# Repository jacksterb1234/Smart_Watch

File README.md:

# Smart Watch — Custom KiCad Smartwatch PCB

A fully custom smartwatch designed from the ground up, featuring a purpose-built PCB, BLE connectivity, and a 3D-printed case. Designed for complete control over hardware and software integration.

> Integration testing projected to begin July 2026.

## Features

- **MCU:** Nordic nRF54L15 — ultra-low power with integrated Bluetooth LE
- **Step counting** via IMU
- **Heart rate sensing**
- **Touchscreen display**
- **Music control** and **notification vibration** (haptic)
- **USB-C charging**
- **Custom 3D-printed case** — ~30% lighter than off-the-shelf alternatives, fully personalizable
- Designed for **JLCPCB assembly**

## Repository Structure

```
Smart_Watch/
├── Architecture.kicad_sch   # Top-level architecture schematic
├── MCU.kicad_sch            # nRF54L15 MCU schematic
├── Power.kicad_sch          # Power management schematic
├── Peripherals.kicad_sch   # Sensors & peripheral schematic
├── Smart_Watch.kicad_pcb   # PCB layout
├── Smart_Watch.pdf          # Full schematic export
├── Smart_Watch.pretty/     # Custom KiCad footprints
├── Smart_Watch.3dshapes/   # 3D models for PCB components
├── ZIF.pretty/              # ZIF connector footprints
├── B2B_PH_SM4_TB/          # Board-to-board connector footprints
├── Backpack_Board/         # Backpack extension board
├── Case/                   # 3D-printable case files
└── jlcpcb/                  # JLCPCB production files (Gerbers, BOM, CPL)
```

## Tools Used

- **KiCad** — Schematic capture and PCB layout
- **JLCPCB** — PCB fabrication and SMT assembly
- **SolidWorks / Fusion360** — Case design

## Key Components

| Component | Function |
|-----------|----------|
| nRF54L15 | MCU with integrated BLE |
| Heart rate sensor | Optical heart rate monitoring |
| IMU | Step counting and motion sensing |
| Touchscreen | User interface display |
| USB-C charger IC | Battery charging via USB-C |

## Author

**Jackson Barber** — [github.com/jacksterb1234](https://github.com/jacksterb1234)

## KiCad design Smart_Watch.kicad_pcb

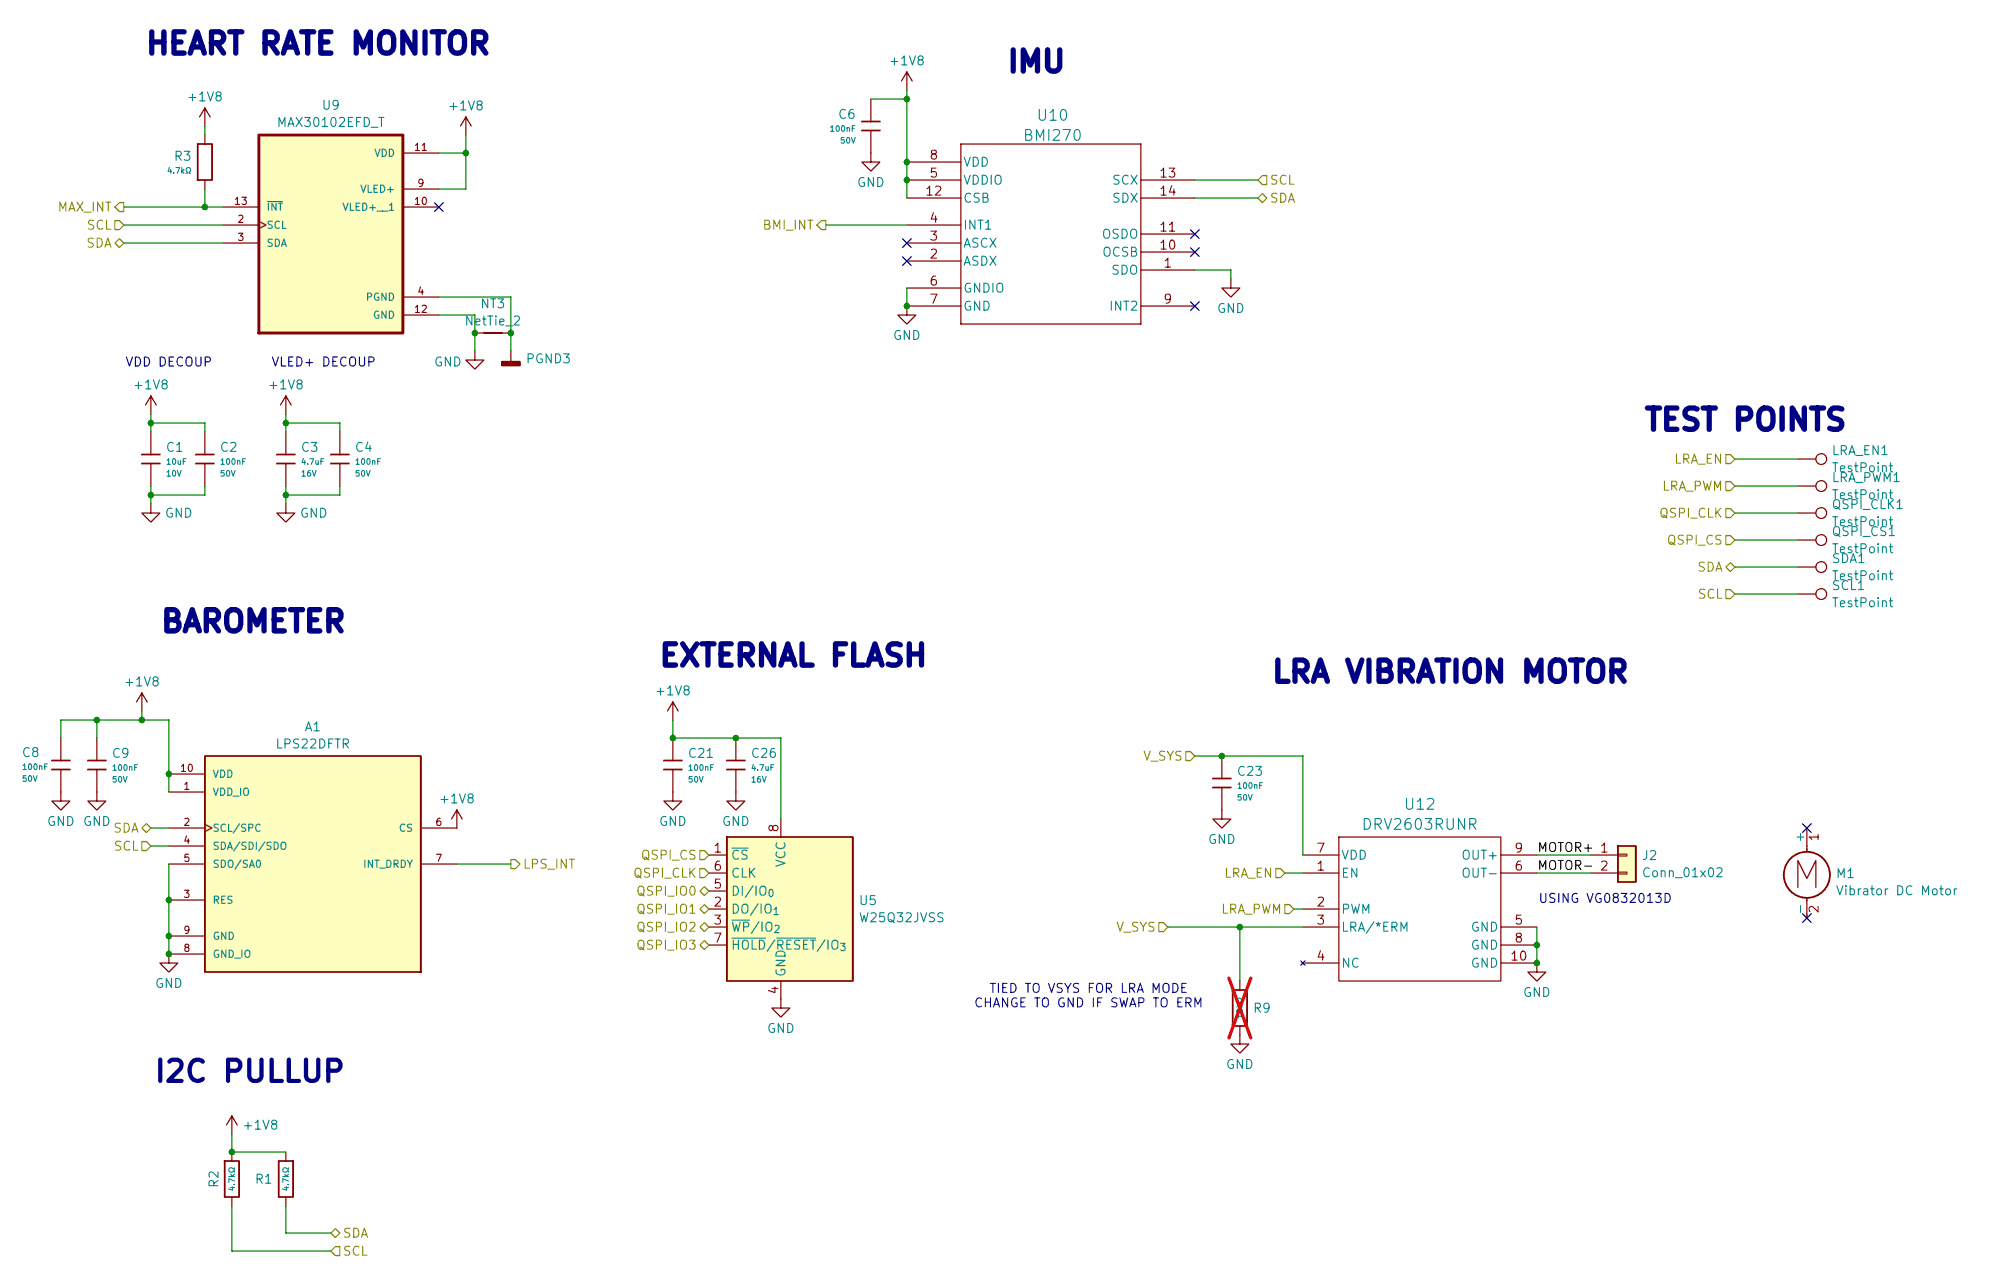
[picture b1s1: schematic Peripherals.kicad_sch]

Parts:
A1: LPS22DFTR; XDCR_LPS22DFTR; PARTREV 3
C1: 10uF; C_0603; Voltage Rated 10V; Tolerance ±10%; Part CL10A106KP8NNNC; LCSC C19702
C2, C4, C6, C8, C9, C21, C23: 100nF; C_0603; Voltage Rated 50V; Tolerance ±10%; Part CC0603KRX7R9BB104; LCSC C14663
C3, C26: 4.7uF; C_0603; Voltage Rated 16V; Tolerance ±10%; Part CL10A475KO8NNNC; LCSC C19666
J2: Conn_01x02; 1x02_1x1mm
LRA_EN1: TestPoint; TestPoint_Pad_1.0x1.0mm
LRA_PWM1: TestPoint; TestPoint_Pad_1.0x1.0mm
M1: Vibrator DC Motor; digikey# 1670-VC1027B902F-ND
NT3: NetTie_2; NetTie-2_SMD_Pad0.5mm
QSPI_CLK1: TestPoint; TestPoint_Pad_1.0x1.0mm
QSPI_CS1: TestPoint; TestPoint_Pad_1.0x1.0mm
R1, R2, R3: 4.7kΩ; R_0603; Overload Voltage (Max) 75V; Tolerance ±1%; Part 0603WAF4701T5E; LCSC C23162
R9: 10kΩ; R_0402; Overload Voltage (Max) 50V; Tolerance ±1%; Part 0402WGF1002TCE; LCSC C25744; not fitted
SCL1: TestPoint; TestPoint_Pad_1.0x1.0mm
SDA1: TestPoint; TestPoint_Pad_1.0x1.0mm
U5: W25Q32JVSS; SOIC-8_5.3x5.3mm_P1.27mm
U9: MAX30102EFD_T; XDCR_MAX30101EFD_
U10: BMI270; BMI270_BOS-L
U12: DRV2603RUNR; RUN10_TEX

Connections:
+1V8: A1.1 (VDD_IO), A1.6 (CS), A1.10 (VDD), C1.2, C2.2, C3.1, C4.1, C6.1, C8.1, C9.1, C21.1, C26.1, R1.1, R2.1, R3.2, U5.8 (VCC), U9.9 (VLED+), U9.11 (VDD), U10.5 (VDDIO), U10.8 (VDD), U10.12 (CSB); also elsewhere on the board
/Architecture/MCU/BMI_INT: U10.4 (INT1); also elsewhere on the board
/Architecture/MCU/LPS_INT: A1.7 (INT_DRDY); also elsewhere on the board
/Architecture/MCU/LRA_EN: LRA_EN1.1 (1_1), U12.1 (EN); also elsewhere on the board
/Architecture/MCU/LRA_PWM: LRA_PWM1.1 (1_1), U12.2 (PWM); also elsewhere on the board
/Architecture/MCU/MAX_INT: R3.1, U9.13 (~INT); also elsewhere on the board
/Architecture/MCU/QSPI_CLK: QSPI_CLK1.1 (1_1), U5.6 (CLK); also elsewhere on the board
/Architecture/MCU/QSPI_CS: QSPI_CS1.1 (1_1), U5.1 (~CS); also elsewhere on the board
/Architecture/MCU/QSPI_IO0: U5.5 (DI/IO_{0}); also elsewhere on the board
/Architecture/MCU/QSPI_IO1: U5.2 (DO/IO_{1}); also elsewhere on the board
/Architecture/MCU/QSPI_IO2: U5.3 (~WP/IO_{2}); also elsewhere on the board
/Architecture/MCU/QSPI_IO3: U5.7 (~HOLD/~RESET/IO_{3}); also elsewhere on the board
/Architecture/MCU/SCL: A1.4 (SDA/SDI/SDO), R2.2, SCL1.1 (1_1), U9.2 (SCL), U10.13 (SCX); also elsewhere on the board
/Architecture/MCU/SDA: A1.2 (SCL/SPC), R1.2, SDA1.1 (1_1), U9.3 (SDA), U10.14 (SDX); also elsewhere on the board
/Architecture/Peripherals/MOTOR+: J2.1, U12.9 (OUT+)
/Architecture/Peripherals/MOTOR-: J2.2, U12.6 (OUT-)
GND: A1.3 (RES), A1.5 (SDO/SA0), A1.8 (GND_IO), A1.9 (GND), C1.1, C2.1, C3.2, C4.2, C6.2, C8.2, C9.2, C21.2, C23.2, C26.2, NT3.1, R9.2, U5.4 (GND), U9.12 (GND), U10.1 (SDO), U10.6 (GNDIO), U10.7 (GND), U12.5 (GND), U12.8 (GND), U12.10 (GND); also elsewhere on the board
PGND3: NT3.2, U9.4 (PGND)
VSYS: C23.1, R9.1, U12.3 (LRA/*ERM), U12.7 (VDD); also elsewhere on the board

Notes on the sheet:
HEART RATE MONITOR
I2C PULLUP
USING VG0832013D
EXTERNAL FLASH
TIED TO VSYS FOR LRA MODE CHANGE TO GND IF SWAP TO ERM
VDD DECOUP
VLED+ DECOUP
BAROMETER
IMU
TEST POINTS
LRA VIBRATION MOTOR

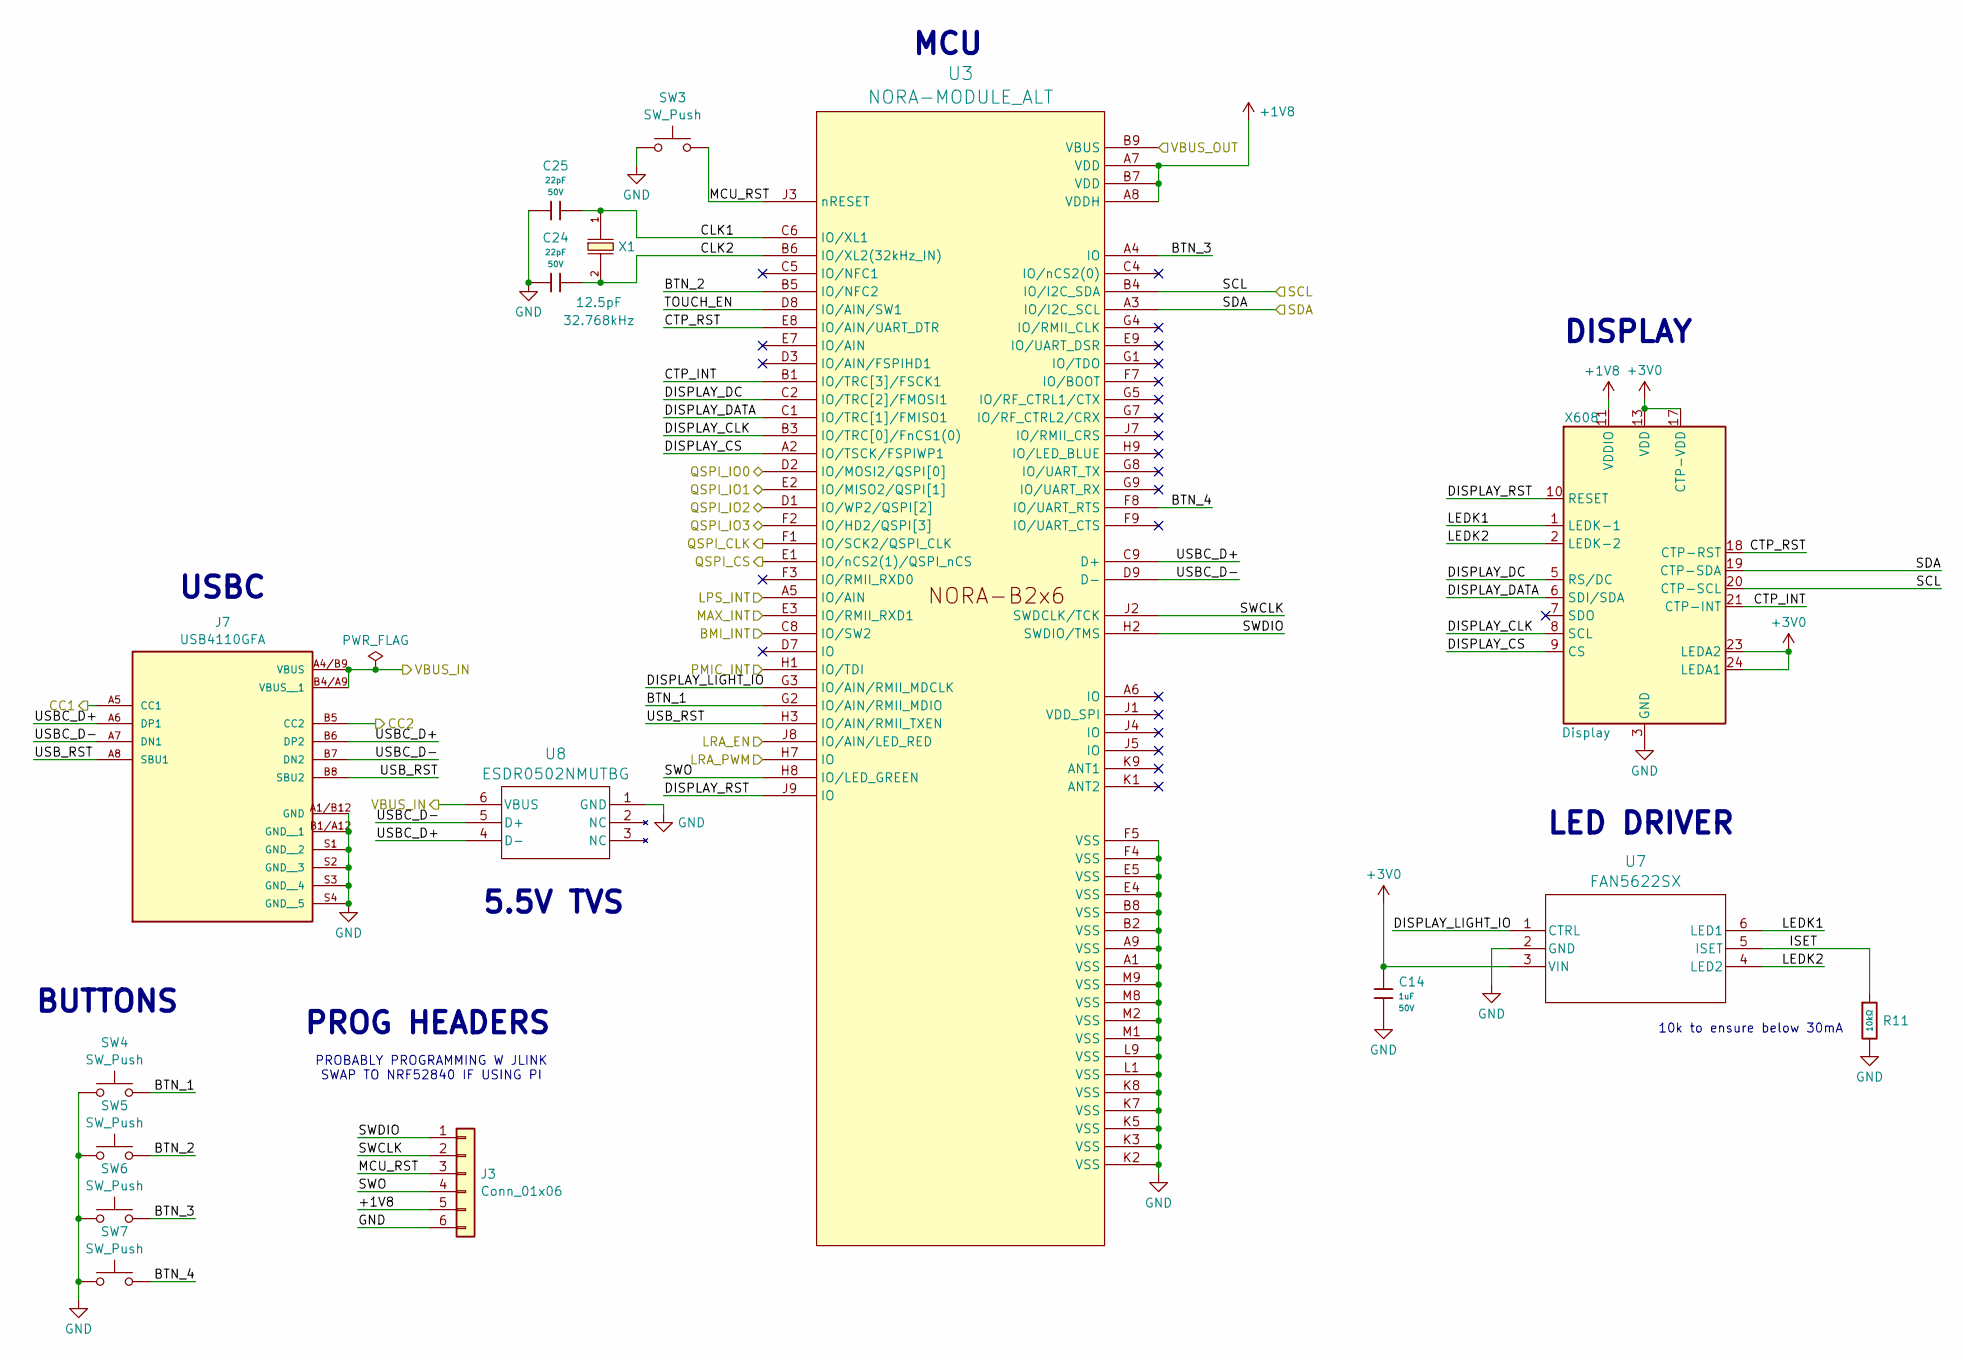
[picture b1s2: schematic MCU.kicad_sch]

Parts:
C14: 1uF; C_0603; Voltage Rated 50V; Tolerance ±10%; Part CL10A105KB8NNNC; LCSC C15849
C24, C25: 22pF; C_0603; Voltage Rated 50V; Tolerance ±5%; Part CL10C220JB8NNNC; LCSC C1653
J3: Conn_01x06; 2x03_1x1mm
J7: USB4110GFA; GCT_USB4110GFA
R11: 10kΩ; R_0603; Overload Voltage (Max) 75V; Tolerance ±1%; Part 0603WAF1002T5E; LCSC C25804
SW3: SW_Push; R_0805_2012Metric
SW4, SW5, SW6, SW7: SW_Push; SW_Push_1P1T-MP_NO_Horizontal_Alps_SKRTLAE010_3D
U3: NORA-MODULE_ALT; NORA_LGA82R_1430X1040X190_ANT; Manufacturer P/N NORA
U7: FAN5622SX; SSOT6_3X1P7_ONS-L
U8: ESDR0502NMUTBG; UDFN6_517AA_ONS-L
X1: Q13FC1350000400; FC-135R_L3.2-W1.5; Frequency Tolerance ±20ppm; Part Q13FC13500004; LCSC C32346
X608: Display; 24-PIN-ZIF

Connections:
+1V8: J3.5, U3.A7 (VDD), U3.A8 (VDDH), U3.B7 (VDD), X608.11 (VDDIO), X608.12 (VDDIO); also elsewhere on the board
+3V0: C14.1, U7.3 (VIN), X608.13 (VDD), X608.14 (VDD), X608.17 (CTP-VDD), X608.23 (LEDA2), X608.24 (LEDA1); also elsewhere on the board
/Architecture/MCU/BMI_INT: U3.C8 (IO/SW2); also elsewhere on the board
/Architecture/MCU/BTN_1: SW4.2, U3.G2 (IO/AIN/RMII_MDIO)
/Architecture/MCU/BTN_2: SW5.2, U3.B5 (IO/NFC2)
/Architecture/MCU/BTN_3: SW6.2, U3.A4 (IO)
/Architecture/MCU/BTN_4: SW7.2, U3.F8 (IO/UART_RTS)
/Architecture/MCU/CC1: J7.A5 (CC1); also elsewhere on the board
/Architecture/MCU/CC2: J7.B5 (CC2); also elsewhere on the board
/Architecture/MCU/CLK1: C25.2, U3.C6 (IO/XL1), X1.1
/Architecture/MCU/CLK2: C24.2, U3.B6 (IO/XL2(32kHz_IN)), X1.2
/Architecture/MCU/CTP_INT: U3.B1 (IO/TRC[3]/FSCK1), X608.21 (CTP-INT)
/Architecture/MCU/CTP_RST: U3.E8 (IO/AIN/UART_DTR), X608.18 (CTP-RST)
/Architecture/MCU/DISPLAY_CLK: U3.B3 (IO/TRC[0]/FnCS1(0)), X608.8 (SCL)
/Architecture/MCU/DISPLAY_CS: U3.A2 (IO/TSCK/FSPIWP1), X608.9 (CS)
/Architecture/MCU/DISPLAY_DATA: U3.C1 (IO/TRC[1]/FMISO1), X608.6 (SDI/SDA)
/Architecture/MCU/DISPLAY_DC: U3.C2 (IO/TRC[2]/FMOSI1), X608.5 (RS/DC)
/Architecture/MCU/DISPLAY_LIGHT_IO: U3.G3 (IO/AIN/RMII_MDCLK), U7.1 (CTRL)
/Architecture/MCU/DISPLAY_RST: U3.J9 (IO), X608.10 (RESET)
/Architecture/MCU/ISET: R11.1, U7.5 (ISET)
/Architecture/MCU/LEDK1: U7.6 (LED1), X608.1 (LEDK-1)
/Architecture/MCU/LEDK2: U7.4 (LED2), X608.2 (LEDK-2)
/Architecture/MCU/LPS_INT: U3.A5 (IO/AIN); also elsewhere on the board
/Architecture/MCU/LRA_EN: U3.J8 (IO/AIN/LED_RED); also elsewhere on the board
/Architecture/MCU/LRA_PWM: U3.H7 (IO); also elsewhere on the board
/Architecture/MCU/MAX_INT: U3.E3 (IO/RMII_RXD1); also elsewhere on the board
/Architecture/MCU/MCU_RST: J3.3, SW3.2, U3.J3 (nRESET)
/Architecture/MCU/PMIC_INT: U3.H1 (IO/TDI); also elsewhere on the board
/Architecture/MCU/QSPI_CLK: U3.F1 (IO/SCK2/QSPI_CLK); also elsewhere on the board
/Architecture/MCU/QSPI_CS: U3.E1 (IO/nCS2(1)/QSPI_nCS); also elsewhere on the board
/Architecture/MCU/QSPI_IO0: U3.D2 (IO/MOSI2/QSPI[0]); also elsewhere on the board
/Architecture/MCU/QSPI_IO1: U3.E2 (IO/MISO2/QSPI[1]); also elsewhere on the board
/Architecture/MCU/QSPI_IO2: U3.D1 (IO/WP2/QSPI[2]); also elsewhere on the board
/Architecture/MCU/QSPI_IO3: U3.F2 (IO/HD2/QSPI[3]); also elsewhere on the board
/Architecture/MCU/SCL: U3.B4 (IO/I2C_SDA), X608.20 (CTP-SCL); also elsewhere on the board
/Architecture/MCU/SDA: U3.A3 (IO/I2C_SCL), X608.19 (CTP-SDA); also elsewhere on the board
/Architecture/MCU/SWCLK: J3.2, U3.J2 (SWDCLK/TCK)
/Architecture/MCU/SWDIO: J3.1, U3.H2 (SWDIO/TMS)
/Architecture/MCU/SWO: J3.4, U3.H8 (IO/LED_GREEN)
/Architecture/MCU/TOUCH_EN: U3.D8 (IO/AIN/SW1)
/Architecture/MCU/USBC_D+: J7.A6 (DP1), J7.B6 (DP2), U3.C9 (D+), U8.4 (D-)
/Architecture/MCU/USBC_D-: J7.A7 (DN1), J7.B7 (DN2), U3.D9 (D-), U8.5 (D+)
/Architecture/MCU/USB_RST: J7.A8 (SBU1), J7.B8 (SBU2), U3.H3 (IO/AIN/RMII_TXEN)
/Architecture/MCU/VBUS_IN: J7.A4/B9 (VBUS), J7.B4/A9 (VBUS__1), U8.6 (VBUS); also elsewhere on the board
/Architecture/MCU/VBUS_OUT: U3.B9 (VBUS); also elsewhere on the board
GND: C14.2, C24.1, C25.1, J3.6, J7.A1/B12 (GND), J7.B1/A12 (GND__1), J7.S1 (GND__2), J7.S2 (GND__3), J7.S3 (GND__4), J7.S4 (GND__5), R11.2, SW3.1, SW4.1, SW5.1, SW6.1, SW7.1, U3.A1 (VSS), U3.A9 (VSS), U3.B2 (VSS), U3.B8 (VSS), U3.E4 (VSS), U3.E5 (VSS), U3.F4 (VSS), U3.F5 (VSS), U3.K2 (VSS), U3.K3 (VSS), U3.K5 (VSS), U3.K7 (VSS), U3.K8 (VSS), U3.L1 (VSS), U3.L9 (VSS), U3.M1 (VSS), U3.M2 (VSS), U3.M8 (VSS), U3.M9 (VSS), U7.2 (GND), U8.1 (GND), X608.3 (GND), X608.4 (GND), X608.15 (GND), X608.16 (GND); also elsewhere on the board

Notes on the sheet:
BUTTONS
DISPLAY
5.5V TVS
USBC
LED DRIVER
10k to ensure below 30mA
MCU
PROBABLY PROGRAMMING W JLINK SWAP TO NRF52840 IF USING PI
PROG HEADERS

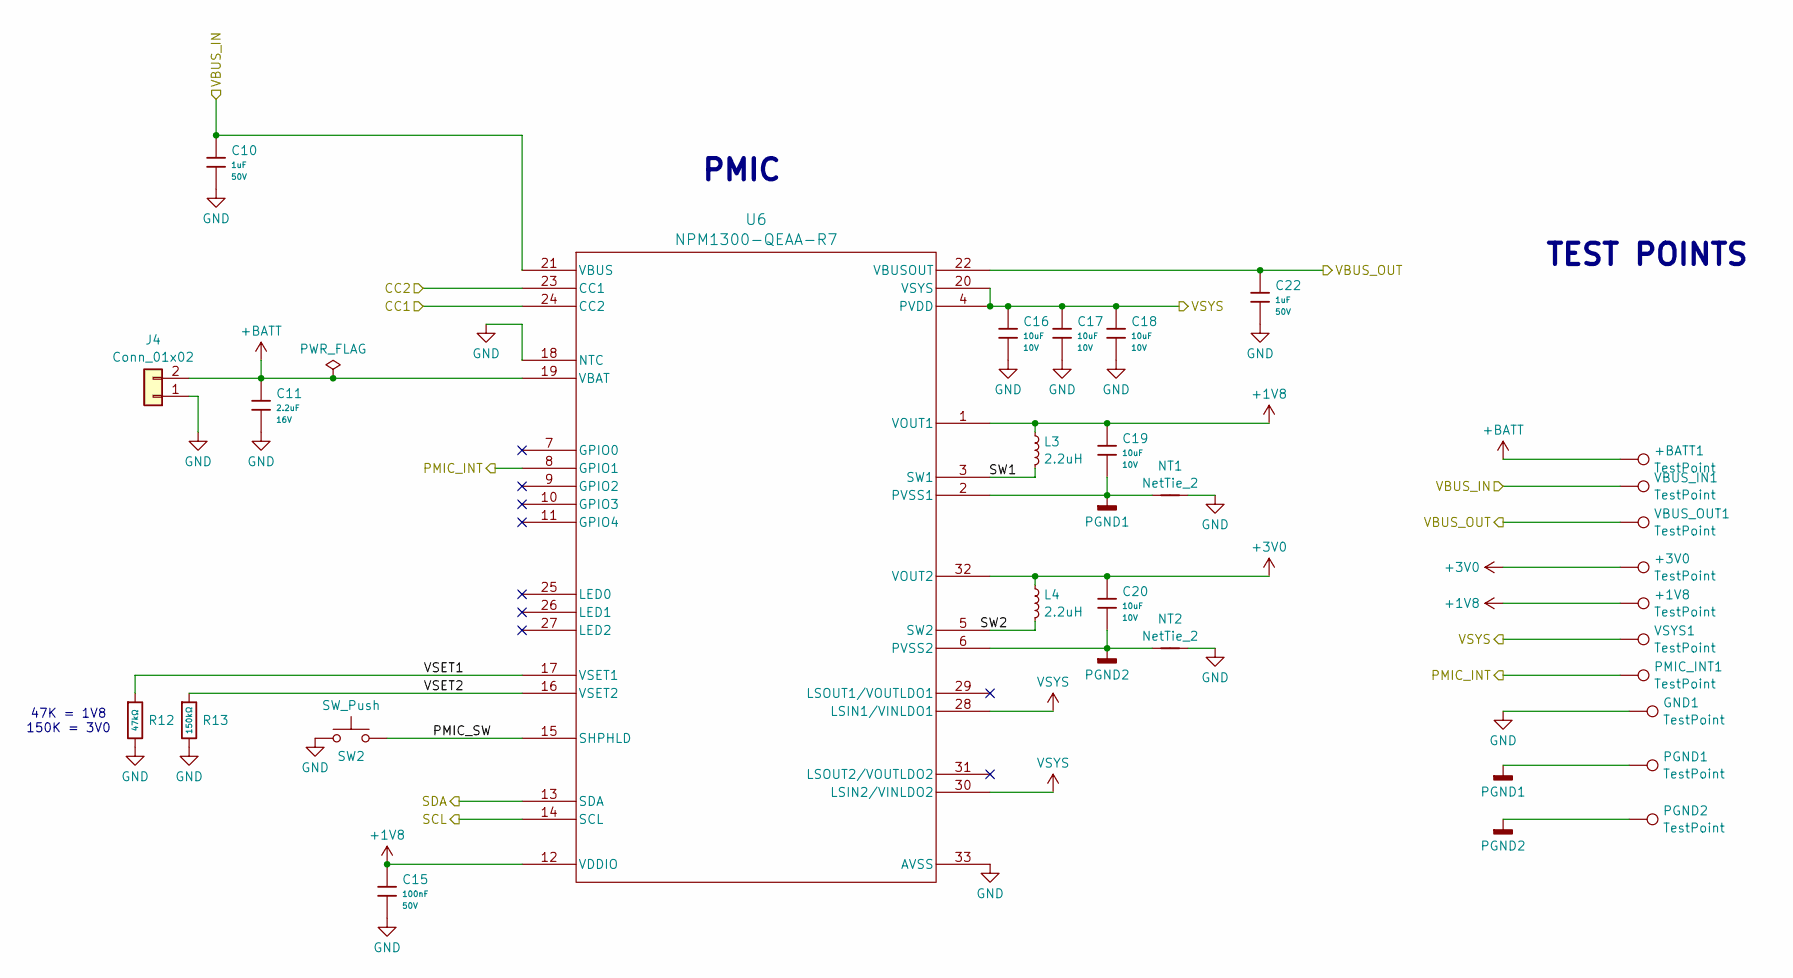
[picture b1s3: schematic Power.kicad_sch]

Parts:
+1V8, +3V0: TestPoint; TestPoint_Pad_1.0x1.0mm
+BATT1: TestPoint; TestPoint_Pad_1.0x1.0mm
C10, C22: 1uF; C_0603; Voltage Rated 50V; Tolerance ±10%; Part CL10A105KB8NNNC; LCSC C15849
C11: 2.2uF; C_0603; Voltage Rated 16V; Tolerance ±10%; Part CL10A225KO8NNNC; LCSC C23630
C15: 100nF; C_0603; Voltage Rated 50V; Tolerance ±10%; Part CC0603KRX7R9BB104; LCSC C14663
C16, C17, C18, C19, C20: 10uF; C_0603; Voltage Rated 10V; Tolerance ±10%; Part CL10A106KP8NNNC; LCSC C19702
GND1: TestPoint; TestPoint_Pad_1.0x1.0mm
J4: Conn_01x02; MOLEX_0781710002
L3, L4: 2.2uH; L_0805_2012Metric; Part DFE201612E-2R2M=P2
NT1, NT2: NetTie_2; NetTie-2_SMD_Pad0.5mm
PGND1, PGND2: TestPoint; TestPoint_Pad_1.0x1.0mm
PMIC_INT1: TestPoint; TestPoint_Pad_1.0x1.0mm
R12: 47kΩ; R_0603; Overload Voltage (Max) 75V; Tolerance ±1%; Part 0603WAF4702T5E; LCSC C25819
R13: 150kΩ; R_0603; Overload Voltage (Max) 75V; Tolerance ±1%; Part 0603WAF1503T5E; LCSC C22807
SW2: SW_Push; R_0805_2012Metric
U6: NPM1300-QEAA-R7; QFN32_5X5_NOR-L
VBUS_IN1: TestPoint; TestPoint_Pad_1.0x1.0mm
VBUS_OUT1: TestPoint; TestPoint_Pad_1.0x1.0mm
VSYS1: TestPoint; TestPoint_Pad_1.0x1.0mm

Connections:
+1V8: +1V8.1 (1_1), C15.1, C19.1, L3.1, U6.1 (VOUT1), U6.12 (VDDIO); also elsewhere on the board
+3V0: +3V0.1 (1_1), C20.1, L4.1, U6.32 (VOUT2); also elsewhere on the board
+BATT: +BATT1.1 (1_1), C11.1, J4.2, U6.19 (VBAT)
/Architecture/MCU/CC1: U6.24 (CC2); also elsewhere on the board
/Architecture/MCU/CC2: U6.23 (CC1); also elsewhere on the board
/Architecture/MCU/PMIC_INT: PMIC_INT1.1 (1_1), U6.8 (GPIO1); also elsewhere on the board
/Architecture/MCU/SCL: U6.14 (SCL); also elsewhere on the board
/Architecture/MCU/SDA: U6.13 (SDA); also elsewhere on the board
/Architecture/MCU/VBUS_IN: C10.1, U6.21 (VBUS), VBUS_IN1.1 (1_1); also elsewhere on the board
/Architecture/MCU/VBUS_OUT: C22.1, U6.22 (VBUSOUT), VBUS_OUT1.1 (1_1); also elsewhere on the board
/Architecture/Power/PMIC_SW: SW2.2, U6.15 (SHPHLD)
/Architecture/Power/SW1: L3.2, U6.3 (SW1)
/Architecture/Power/SW2: L4.2, U6.5 (SW2)
/Architecture/Power/VSET1: R12.1, U6.17 (VSET1)
/Architecture/Power/VSET2: R13.1, U6.16 (VSET2)
GND: C10.2, C11.2, C15.2, C16.2, C17.2, C18.2, C22.2, GND1.1 (1_1), J4.1, NT1.2, NT2.2, R12.2, R13.2, SW2.1, U6.18 (NTC), U6.33 (AVSS); also elsewhere on the board
PGND1: C19.2, NT1.1, PGND1.1 (1_1), U6.2 (PVSS1)
PGND2: C20.2, NT2.1, PGND2.1 (1_1), U6.6 (PVSS2)
VSYS: C16.1, C17.1, C18.1, U6.4 (PVDD), U6.20 (VSYS), U6.28 (LSIN1/VINLDO1), U6.30 (LSIN2/VINLDO2), VSYS1.1 (1_1); also elsewhere on the board

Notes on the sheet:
TEST POINTS
47K = 1V8 150K = 3V0
PMIC

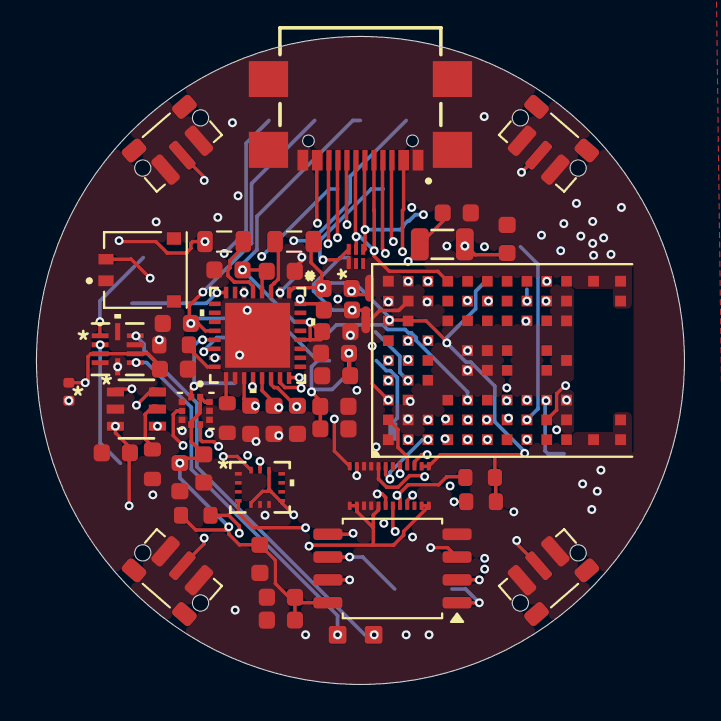
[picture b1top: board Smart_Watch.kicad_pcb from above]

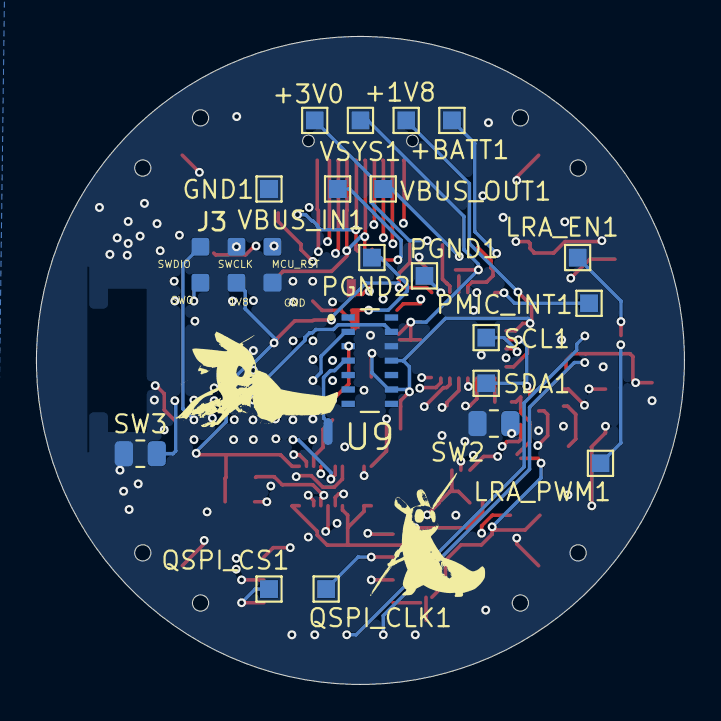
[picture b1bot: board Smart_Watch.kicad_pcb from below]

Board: 4 copper layers, 36.0 x 36.0 mm, 71 parts (21 on the bottom side), 57 nets.

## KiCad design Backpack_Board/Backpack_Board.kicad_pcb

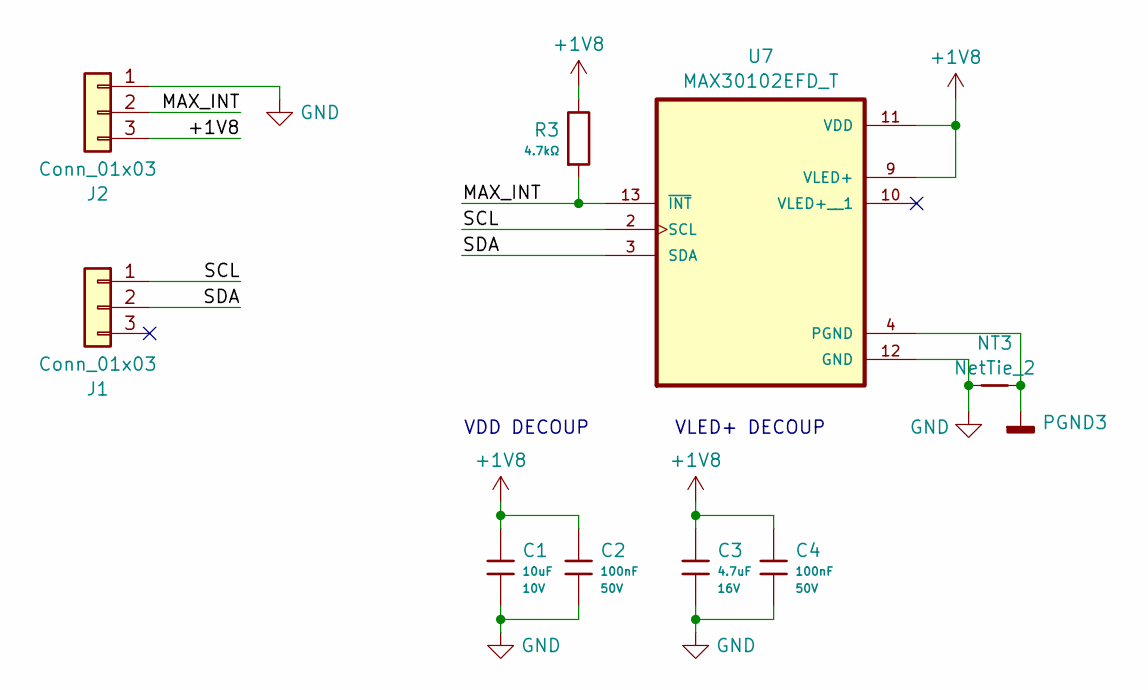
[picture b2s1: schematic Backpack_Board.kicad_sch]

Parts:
C1: 10uF; C_0603; Voltage Rated 10V; Tolerance ±10%; Part CL10A106KP8NNNC; LCSC C19702
C2, C4: 100nF; C_0603; Voltage Rated 50V; Tolerance ±10%; Part CC0603KRX7R9BB104; LCSC C14663
C3: 4.7uF; C_0603; Voltage Rated 16V; Tolerance ±10%; Part CL10A475KO8NNNC; LCSC C19666
J1, J2: Conn_01x03; PinHeader_1x03_P1.27mm_Vertical
NT3: NetTie_2; NetTie-2_SMD_Pad0.5mm
R3: 4.7kΩ; R_0603; Overload Voltage (Max) 75V; Tolerance ±1%; Part 0603WAF4701T5E; LCSC C23162
U7: MAX30102EFD_T; XDCR_MAX30101EFD_

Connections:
+1V8: C1.2, C2.2, C3.1, C4.1, J2.3, R3.2, U7.9 (VLED+), U7.11 (VDD)
/MAX_INT: J2.2, R3.1, U7.13 (~INT)
/SCL: J1.1, U7.2 (SCL)
/SDA: J1.2, U7.3 (SDA)
GND: C1.1, C2.1, C3.2, C4.2, J2.1, NT3.1, U7.12 (GND)
PGND3: NT3.2, U7.4 (PGND)

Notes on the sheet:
VLED+ DECOUP
VDD DECOUP

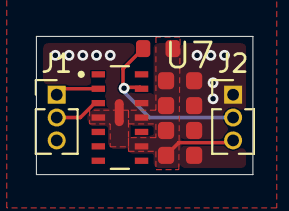
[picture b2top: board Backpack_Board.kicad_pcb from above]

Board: 2 copper layers, 12.0 x 7.7 mm, 9 parts (0 on the bottom side), 6 nets.

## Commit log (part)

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2026-04-08 Worked on peripheral schem
2026-04-08 Added flash
2026-04-09 Updated power and MCU schem
2026-04-11 PMIC integration
2026-04-12 Updated MCU
2026-04-13 Fixed Hierarchical Labels
2026-04-14 Added Vibration Motor & Prog Pinout
2026-04-16 Added clock and updated schem
2026-04-21 Updated Schem and Organized Layout
2026-04-25 Layout V1
2026-04-27 I hate you git
2026-04-27 Fix repo problems
2026-04-28 Remove backups folder
2026-04-28 Update most sym/footprint libraries
2026-04-28 Remove remaining .kicad_prl files
2026-04-29 Added Backpack Board
2026-04-29 WIP changes
2026-04-29 Switch inductors
2026-04-29 Change more footprints
2026-04-29 Completed Backpack Board
2026-04-29 Remove heart rate sensor from main board
2026-04-29 Update the last components and change a couple
2026-04-29 Added Backpack Integration + Layout V1
2026-04-29 Layout Midpoint, Updated Backpack Schem
2026-04-29 USB Layout Updates
2026-04-30 Routing V1 Complete!
2026-04-30 PCB V1 Complete!
2026-04-30 Updated Keepout and Started Case Model
2026-05-01 Began Backpack Removal to Lower Profile
2026-05-01 Flipped switches + Heart Rate, Moving Battery
2026-05-01 Everything but ZIF moved
2026-05-01 Everything Moved to Front
2026-05-01 Restore deleted files
2026-05-01 Restored Too Many Files D:
2026-05-01 Updated ZIF Keepout & Cleaned Trace Routing
2026-05-04 Edited Switch & MCU Location to Fit Case
2026-05-05 Added Test Points and Changed to Top Mounted USBC
2026-05-07 Small Updates
2026-05-07 Fix some ERC problems
2026-05-07 New Case Files + Updated DRC Errors
2026-05-17 Replaced unavailable JLC components
2026-05-18 Updated DRC Errors & More JLC Changes
2026-05-21 Replaced b106 w b206 for jlc compatibility
2026-05-21 Updated Layout for B206
2026-05-25 Updated Layout
2026-05-26 Swapped back to smaller Barometer + IMU
2026-05-27 Cleanup
2026-05-29 Removed amb light, extended board for usbc and buttons
2026-05-30 Add README
    Added detailed project description, features, repository structure, tools used, key components, and author information to README.
2026-06-05 Everything fits on front!
